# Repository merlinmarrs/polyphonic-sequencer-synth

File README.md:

# polyphonic-sequencer-synth

**WARNING: This device could destroy your computer's USB port or USB adapter. This device also flashes at high frequency and is an epilepsy risk.**

*NOTE: Not all 74HC14 ICs work for this circuit. Elliot Williams uses the CD40106BE instead. Make sure your 74HC14 has Schmitt trigger with hysteresis and maybe order a couple different brands to be sure. I find that Nexperia ICs work well and not I have had bad luck with Diodes Incorporated.

A mini sequencer and polyphonic synth based directly on Elliot Williams' epic Logic Noise series from Hackaday (https://hackaday.com/2015/02/04/logic-noise-sweet-sweet-oscillator-sounds/).

The boards were designed and manufactured at Fablab Digiscope in Orsay France, which is run by Romain Di Vozzo, by Jonah Marrs with funding from La Diagonale U Paris Saclay. Here's a video of the workshop and the board in action: https://vimeo.com/653720316

Selena Pere has made an beautiful inferface for a version 2 of this device. 

The sequencer portion is an 8-bit looper using a 595 shift register (and a second 595 just to make the corresponding LEDs blink). Bits can be added in LOOP mode by pushing the BEAT button. Beats are automatically added in AUTO mode by synchronizing the CLK and DATA knobs at the far right. The green LED is connected to the CLK frequency. 

The jumpers can trigger one of three notes everytime that corresponding LED flashes. The timber of each note can be varied by turning the pots marked A, B and C. 

The notes are passively mixed in a final stage and can be either output to the onboard buzzer or send to the 3.5mm audio out with OUT selected on the second slide switch. 

The board can be powered by USB C or with a 5V power supply connected to the power header. 

Notes:
-For the device to make predictable sound, there should be at least one jumper going to notes A, B and C from the loop sequence header. 
-If the clock is set too fast it will saturate the shift register resulting in a full set of beats. To remove the beats, turn to AUTO mode and find a combination of CLK and DATA that produces no beats, and then switch back to LOOP mode once the beats have been cleared to make your own pattern. 
-You have to push down hard enough to activate the mini metal button and if the clock is going super slow it might seem likes it's impossible to add beats. Either speed up the CLK or hold the button longer than you would expect is necessary :).
-If you change the output mixing resistors you can change the output volume.

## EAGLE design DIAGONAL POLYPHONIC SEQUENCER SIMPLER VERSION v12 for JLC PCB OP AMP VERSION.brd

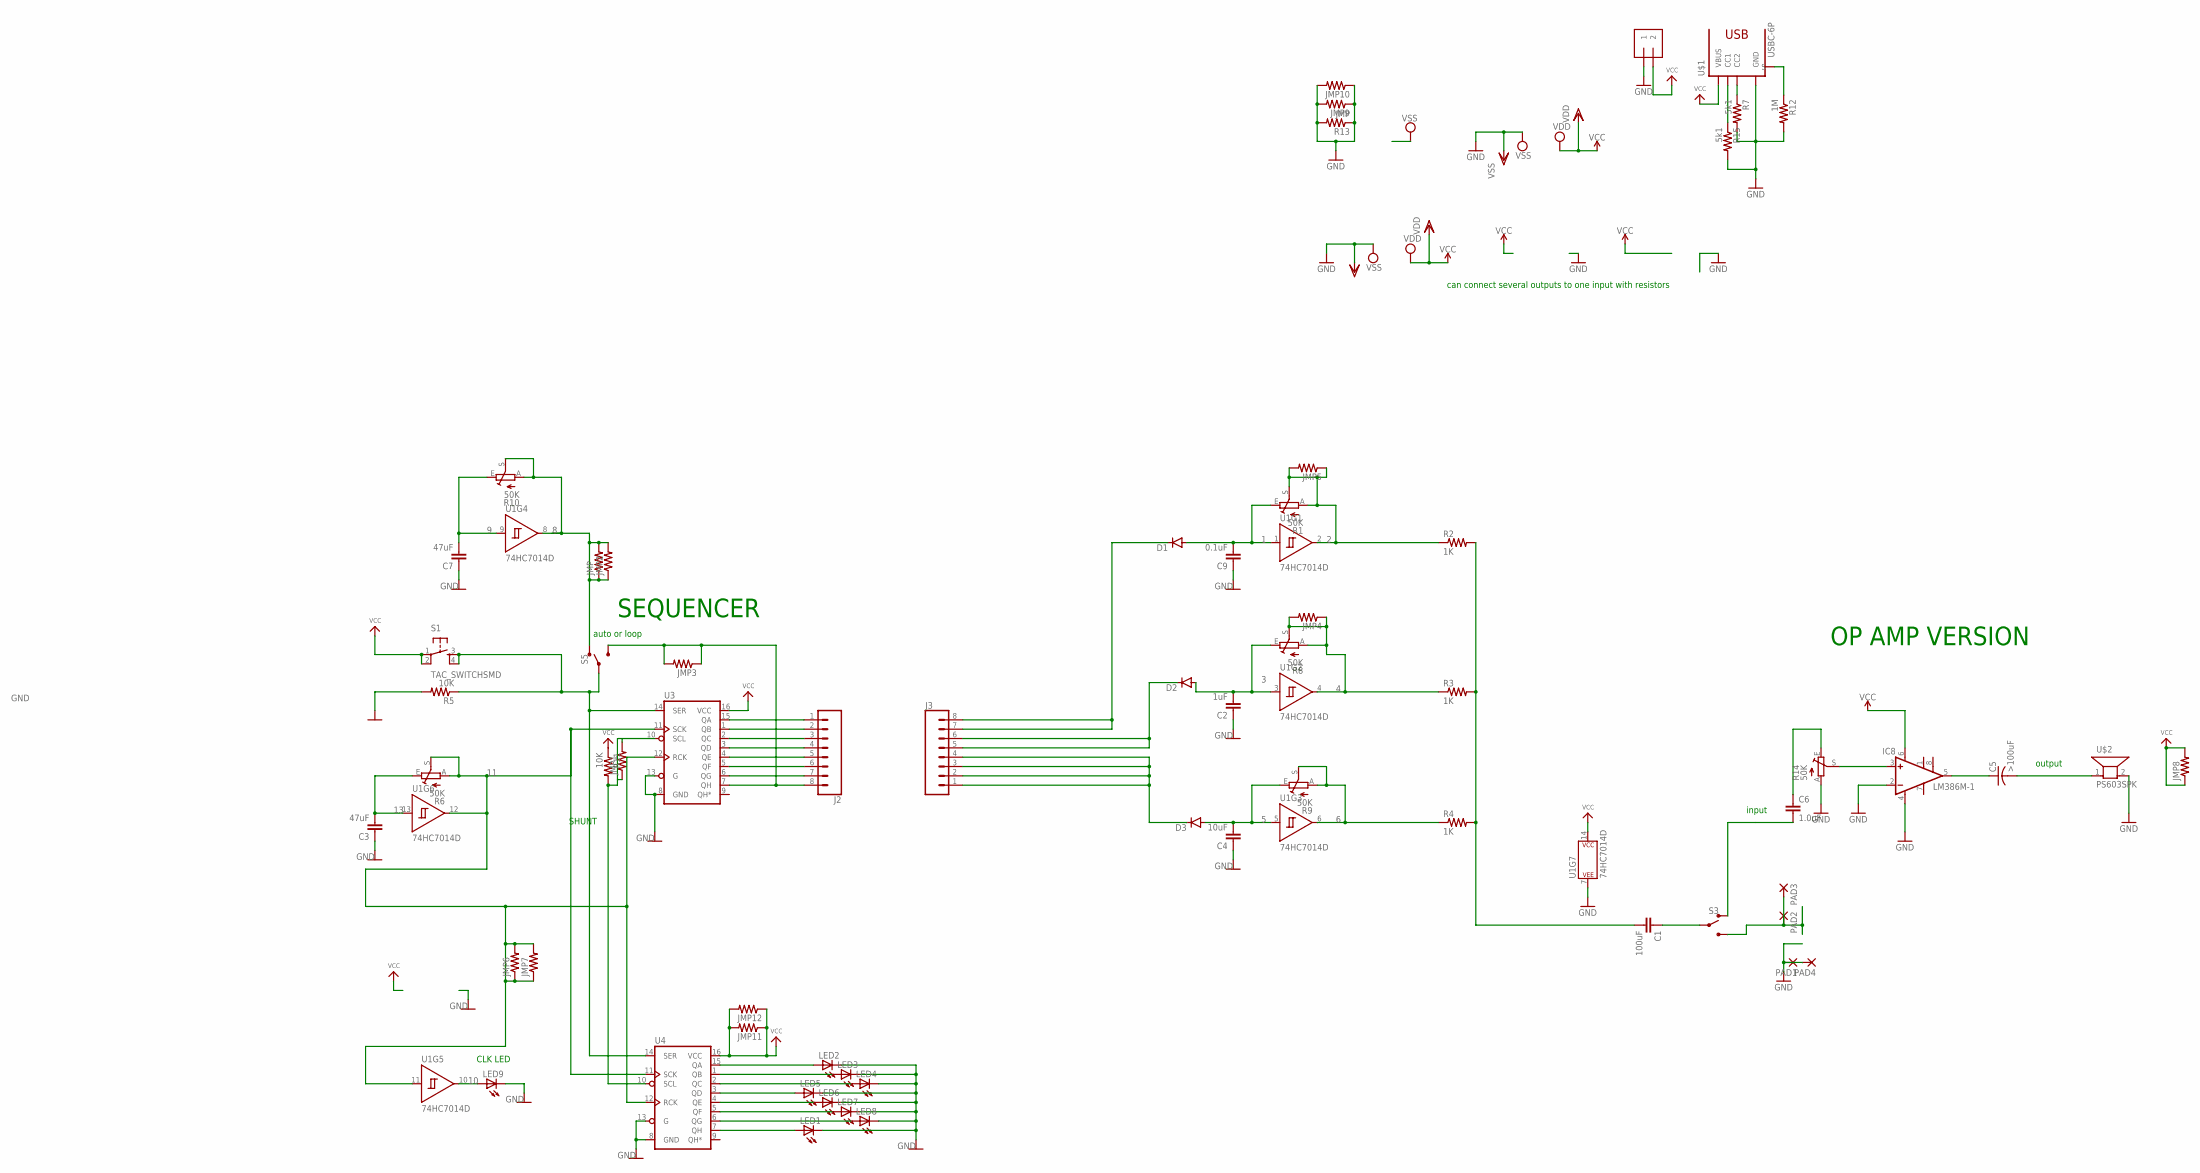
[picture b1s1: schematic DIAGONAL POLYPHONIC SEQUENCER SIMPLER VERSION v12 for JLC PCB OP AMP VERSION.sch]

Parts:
C1: 100uF; 1206
C2: 1uF; 1206
C3, C7: 47uF; 1206
C4: 10uF; 1206
C5: >100uF; C1206
C6: 1.0uF; 1206
C9: 0.1uF; 1206
D1, D2, D3: DIODEDO214AA; DO-214AA
IC8: LM386M-1; SO08
J1: 1X2-3.5MM
J2, J3: CONN_08SMD-STRAIGHT-ALT-FEMALE; 1X08_SMD_ALT
JMP, JMP1, JMP2, JMP3, JMP4, JMP5, JMP6, JMP7, JMP8, JMP9, JMP10, JMP11, JMP12: R-US_R1206; R1206
LED1, LED2, LED3, LED4, LED5, LED6, LED7, LED8, LED9: LEDCHIPLED_1206; CHIPLED_1206
PAD1, PAD2, PAD3, PAD4: SMD5; SMD2,54-5,08
R1, R6, R8, R9, R10, R14: 50K; CA9V
R2, R3, R4: 1K; R1206
R5, R11: 10K; R1206
R7, R15: 5k1; R1206
R12: 1M; R1206
R13: JMP; R1206
S1: TAC_SWITCHSMD; TACTILE-SWITCH-SMD
S3, S5: SWITCH-SPDT-SMD-AYZ0202; SWITCH_DPDT_SMD_AYZ0202
U1: 74HC7014D; SO14
U3, U4: 74595; TSSOP16
U$1: USBC-6P; USCX-06FX-XXMX-01
U$2: PS603SPK; PS603

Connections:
1: C9.2, D1.A, R1.E, U1.1 (A)
2: JMP5.1, JMP5.2, R1.A, R1.S, R2.1, U1.2 (Y)
3: C2.2, D2.A, R8.E, U1.3 (A)
4: JMP4.1, JMP4.2, R3.1, R8.A, R8.S, U1.4 (Y)
5: C4.2, D3.A, R9.E, U1.5 (A)
6: R4.1, R9.A, R9.S, U1.6 (Y)
8: JMP.1, JMP.2, JMP2.1, JMP2.2, R10.A, R10.S, S5.1 (O), U1.8 (Y)
9: C7.2, R10.E, U1.9 (A)
10: LED9.A, U1.10 (Y)
11: JMP6.1, JMP6.2, JMP7.1, JMP7.2, R6.A, R6.S, U1.11 (A), U1.12 (Y), U3.11 (SCK), U3.12 (RCK), U4.11 (SCK), U4.12 (RCK)
13: C3.2, R6.E, U1.13 (A)
GND: C2.1, C3.1, C4.1, C7.1, C9.1, IC8.2 (-IN), IC8.4 (GND), J1.1, JMP9.1, JMP9.2, JMP10.1, JMP10.2, LED1.C, LED2.C, LED3.C, LED4.C, LED5.C, LED6.C, LED7.C, LED8.C, LED9.C, PAD1.1, PAD4.1, R5.2, R7.2, R12.2, R13.1, R13.2, R14.A, R15.2, U1.7 (P$V-), U3.8 (GND), U3.13 (G), U4.8 (GND), U4.13 (G), U$1.GND1 (GND), U$1.GND2 (GND), U$2.2
unnamed: LED1.A, U4.7 (QH)
unnamed: C1.2, R2.2, R3.2, R4.2
unnamed: LED4.A, U4.2 (QC)
unnamed: R7.1, U$1.CC2
unnamed: LED2.A, U4.15 (QA)
unnamed: LED3.A, U4.1 (QB)
unnamed: C1.1, S3.2
unnamed: J2.1, U3.15 (QA)
unnamed: J2.2, U3.1 (QB)
unnamed: LED7.A, U4.5 (QF)
unnamed: LED6.A, U4.4 (QE)
unnamed: LED8.A, U4.6 (QG)
unnamed: LED5.A, U4.3 (QD)
unnamed: D3.C, J3.1, J3.2, J3.3, J3.4
unnamed: D2.C, J3.5, J3.6
unnamed: R15.1, U$1.CC1
unnamed: J2.3, U3.2 (QC)
unnamed: PAD2.1, PAD3.1, S3.3 (S)
unnamed: C6.2, S3.1 (O)
unnamed: J2.4, U3.3 (QD)
unnamed: R12.1, U$1.SHIELD1 (S), U$1.SHIELD2 (S), U$1.SHIELD3 (S), U$1.SHIELD4 (S)
unnamed: D1.C, J3.7, J3.8
unnamed: J2.5, U3.4 (QE)
unnamed: J2.6, U3.5 (QF)
unnamed: J2.7, U3.6 (QG)
unnamed: J2.8, JMP3.1, JMP3.2, S5.3 (S), U3.7 (QH)
unnamed: R5.1, S1.3, S1.4, S5.2, U3.14 (SER), U4.14 (SER)
unnamed: JMP1.1, JMP1.2, R11.2, U3.10 (SCL), U4.10 (SCL)
unnamed: IC8.3 (+IN), R14.S
unnamed: C5.1, IC8.5 (OUT)
unnamed: C5.2, U$2.1
unnamed: C6.1, R14.E
VCC: IC8.6 (VS), J1.2, JMP8.1, JMP8.2, JMP11.1, JMP11.2, JMP12.1, JMP12.2, R11.1, S1.1, S1.2, U1.14 (P$V+), U3.16 (VCC), U4.16 (VCC), U$1.VBUS1 (VBUS), U$1.VBUS2 (VBUS)

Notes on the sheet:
auto or loop
can connect several outputs to one input with resistors
SEQUENCER
SHUNT
CLK LED
input
output
OP AMP VERSION

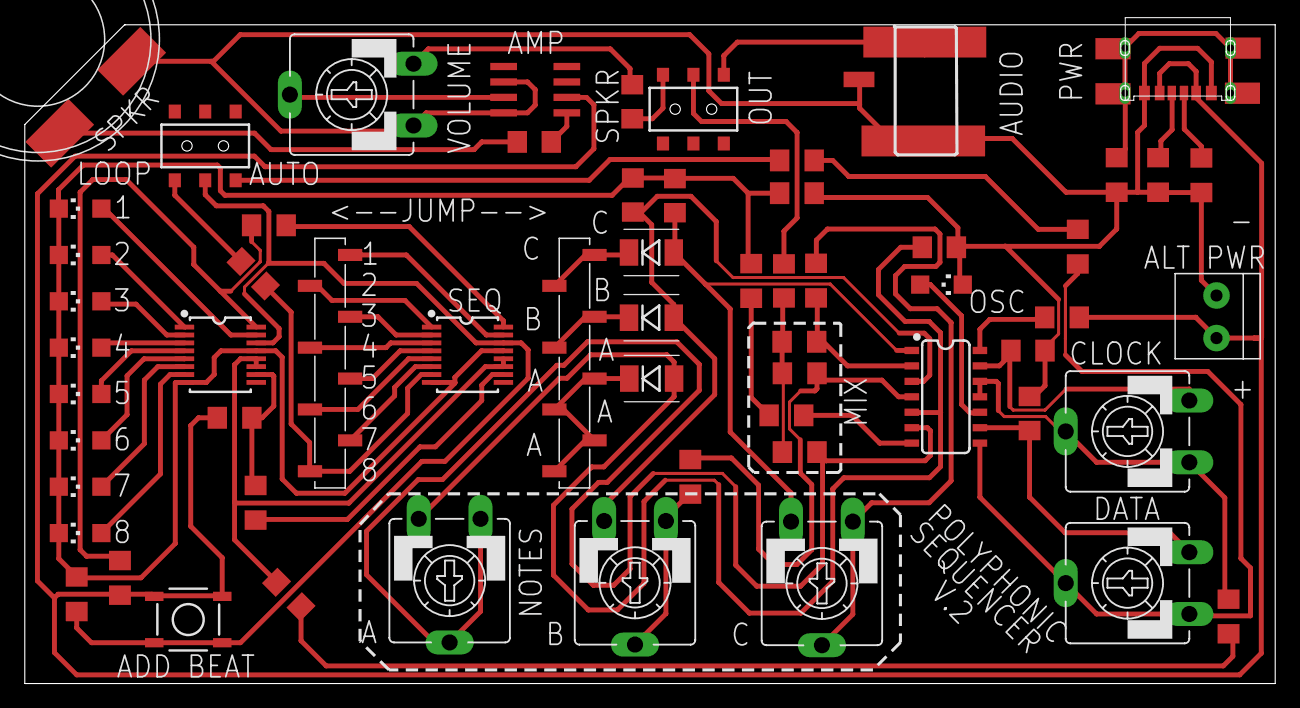
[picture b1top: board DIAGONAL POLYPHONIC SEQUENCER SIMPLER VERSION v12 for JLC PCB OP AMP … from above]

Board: 2 copper layers, 102.8 x 54.2 mm, 64 parts (0 on the bottom side), 45 nets.

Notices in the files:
parts and their libraries:
SparkFun-Connectors: Licensing: Creative Commons ShareAlike 4.0 International - https://creativecommons.org/licenses/by-sa/4.0
